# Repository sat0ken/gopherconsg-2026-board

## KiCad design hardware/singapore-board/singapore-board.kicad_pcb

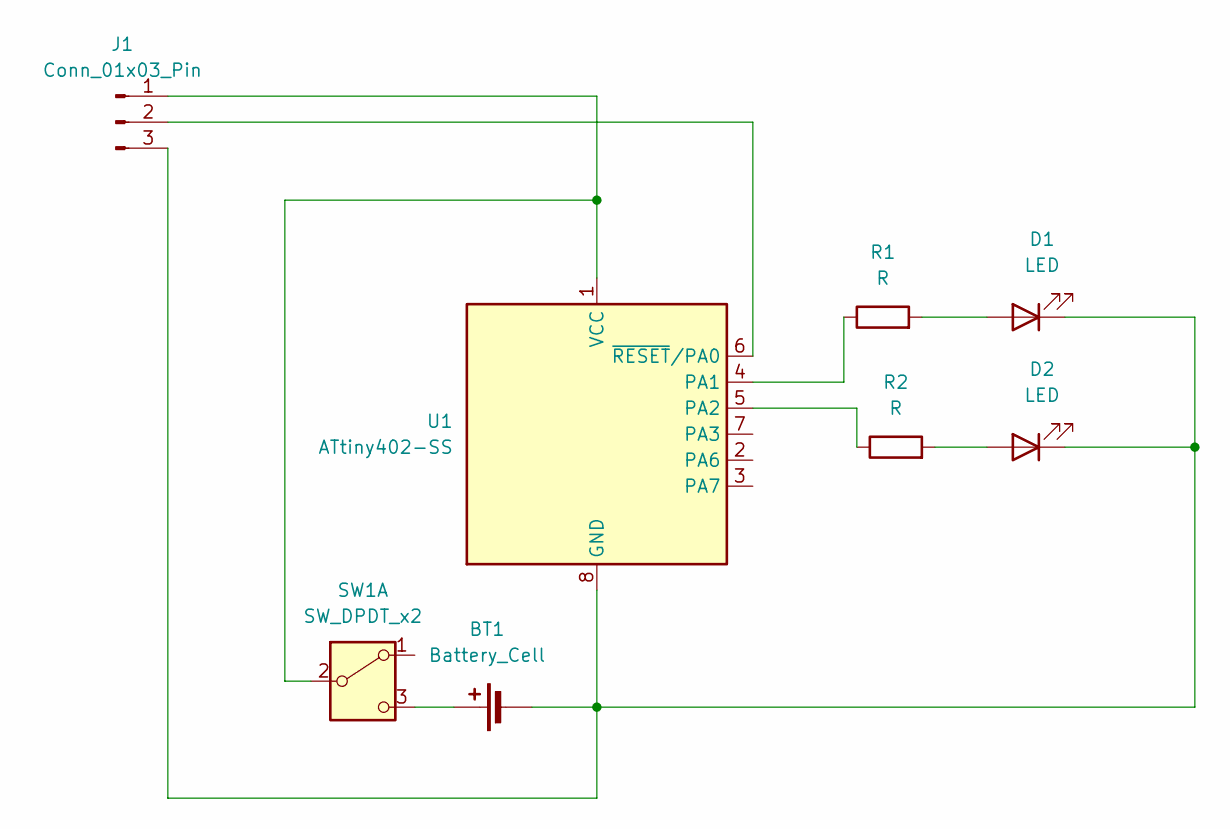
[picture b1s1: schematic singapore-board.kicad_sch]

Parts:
BT1: Battery_Cell; BatteryHolder_Multicomp_BC-2001_1x2032
D1, D2: LED; LED_D3.0mm
J1: Conn_01x03_Pin; PinHeader_1x03_P2.54mm_Vertical
R1, R2: R; R_Axial_DIN0204_L3.6mm_D1.6mm_P5.08mm_Horizontal
SW1: SW_DPDT_x2; PinSocket_1x03_P2.54mm_Vertical
U1: ATtiny402-SS; SOIC-8_3.9x4.9mm_P1.27mm

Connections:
unnamed: BT1.1 (+), SW1.3 (C)
unnamed: BT1.2 (-), D1.1 (K), D2.1 (K), J1.3, U1.8 (GND)
unnamed: D1.2 (A), R1.2
unnamed: D2.2 (A), R2.2
unnamed: J1.1, SW1.2 (B), U1.1 (VCC)
unnamed: J1.2, U1.6 (~RESET/PA0)
unnamed: R1.1, U1.4 (PA1)
unnamed: R2.1, U1.5 (PA2)

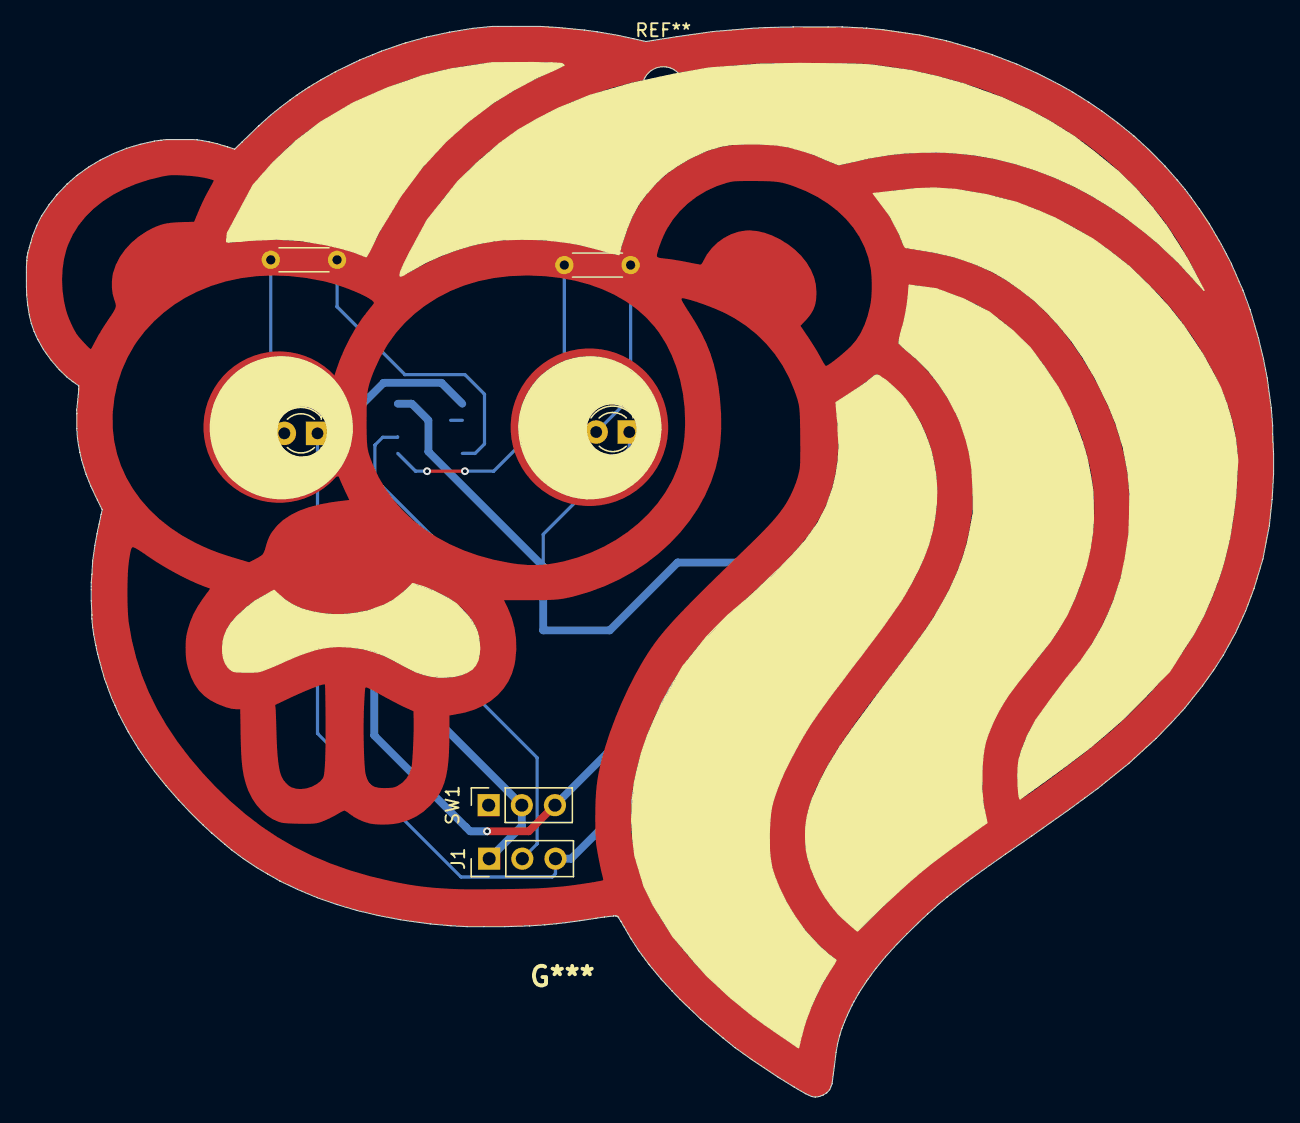
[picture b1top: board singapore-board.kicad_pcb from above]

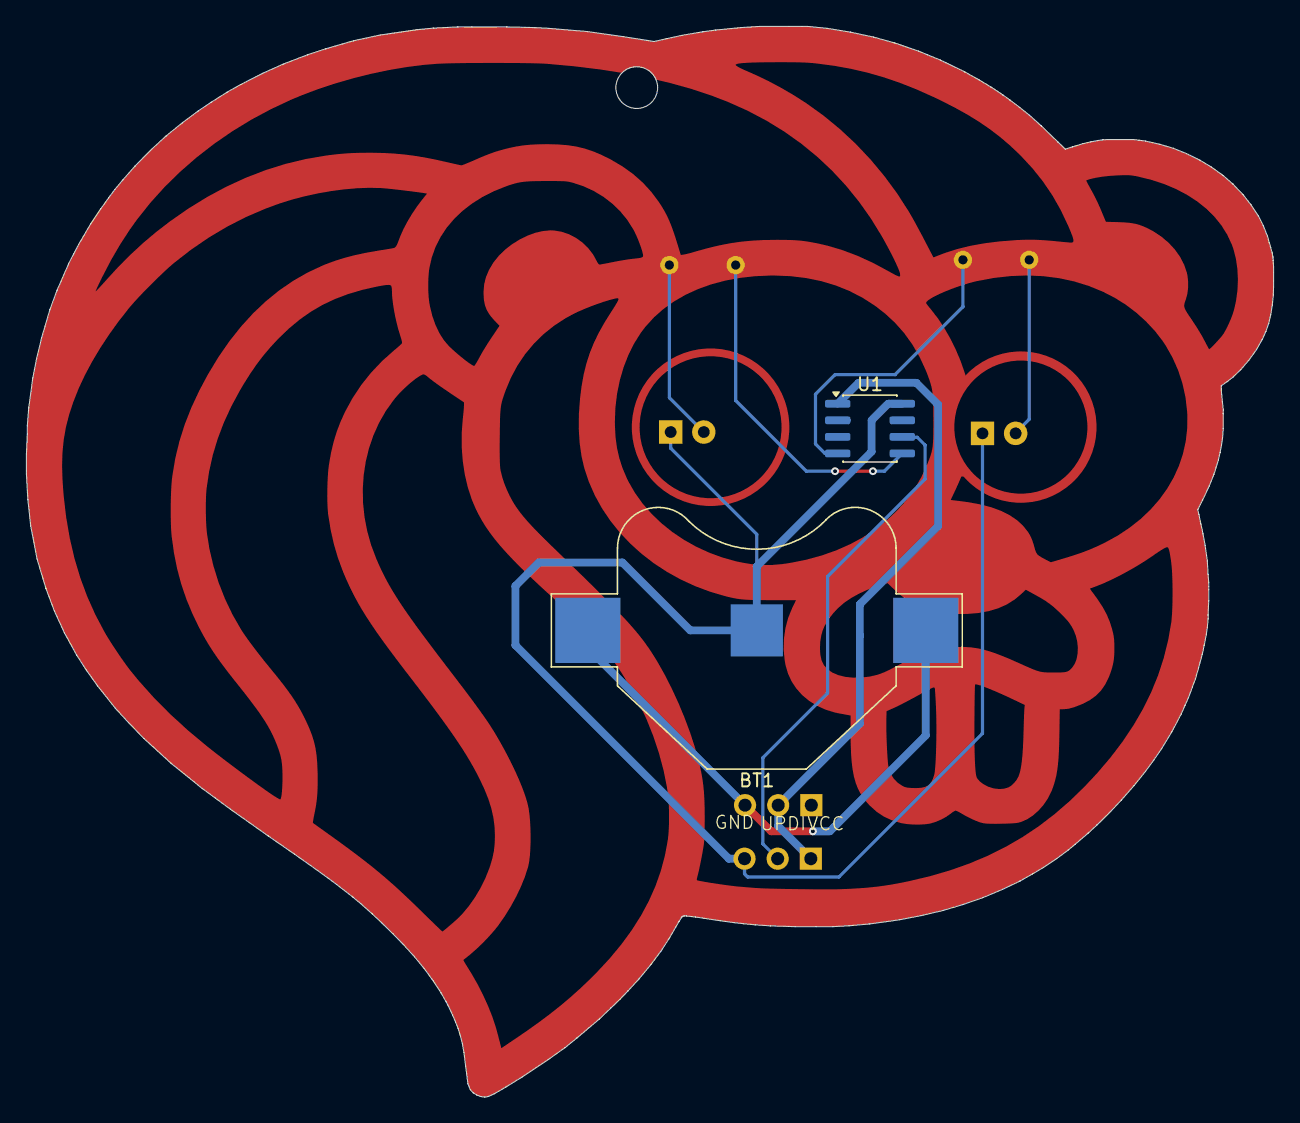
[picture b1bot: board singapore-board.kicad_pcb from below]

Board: 2 copper layers, 95.6 x 82.1 mm, 8 parts (2 on the bottom side), 8 nets.

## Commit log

2026-05-27 add kicad files
2026-06-03 remove files
